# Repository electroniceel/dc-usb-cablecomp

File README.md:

12 VDC to Vusb adapter with compensation for cable resistance
=============================================================

Use a reliable 12 VDC power supply for USB-powered devices.

Dedicated USB chargers often don't have the desired reliability 
for 24/7 use over several years. Power supplies with 12 VDC output
into a DC jack are available in a reliable quality. I can recommend
Meanwell GST40A12-P1J.

USB cables often have higher resistance than
dedicated power cables, even the better ones designed for charging.
This leads to significant voltage drop at higher loads and can cause
the devices to become unstable. Also charging phones is often slower
due to the voltage drop. This adapter compensates for this by sligtly 
increasing the voltage with increasing load.

Schematics & Layout
-------------------

Schematics & Layout were done in KiCAD.

[Schematics as PDF](https://github.com/electroniceel/dc-usb-cablecomp/raw/master/schematics.pdf)

Case
----

I designed the adapter with heatshrink tube as case in mind. I used
heatshrink tube with 24mm unshrunk diameter, hotglue inside and 4:1 shrink ratio.

The label on my heatshrink tube says "PLDW 104-24/6", Reichelt order number "SDK 24,0 SW".

I cut a strip of 42mm, which fits well after shrinking.

License
-------

This work is licensed under a [Creative Commons Attribution 4.0 International License](https://creativecommons.org/licenses/by/4.0/).

Please link to https://github.com/electroniceel/dc-usb-cablecomp or https://git.io/JfeTQ for attribution.

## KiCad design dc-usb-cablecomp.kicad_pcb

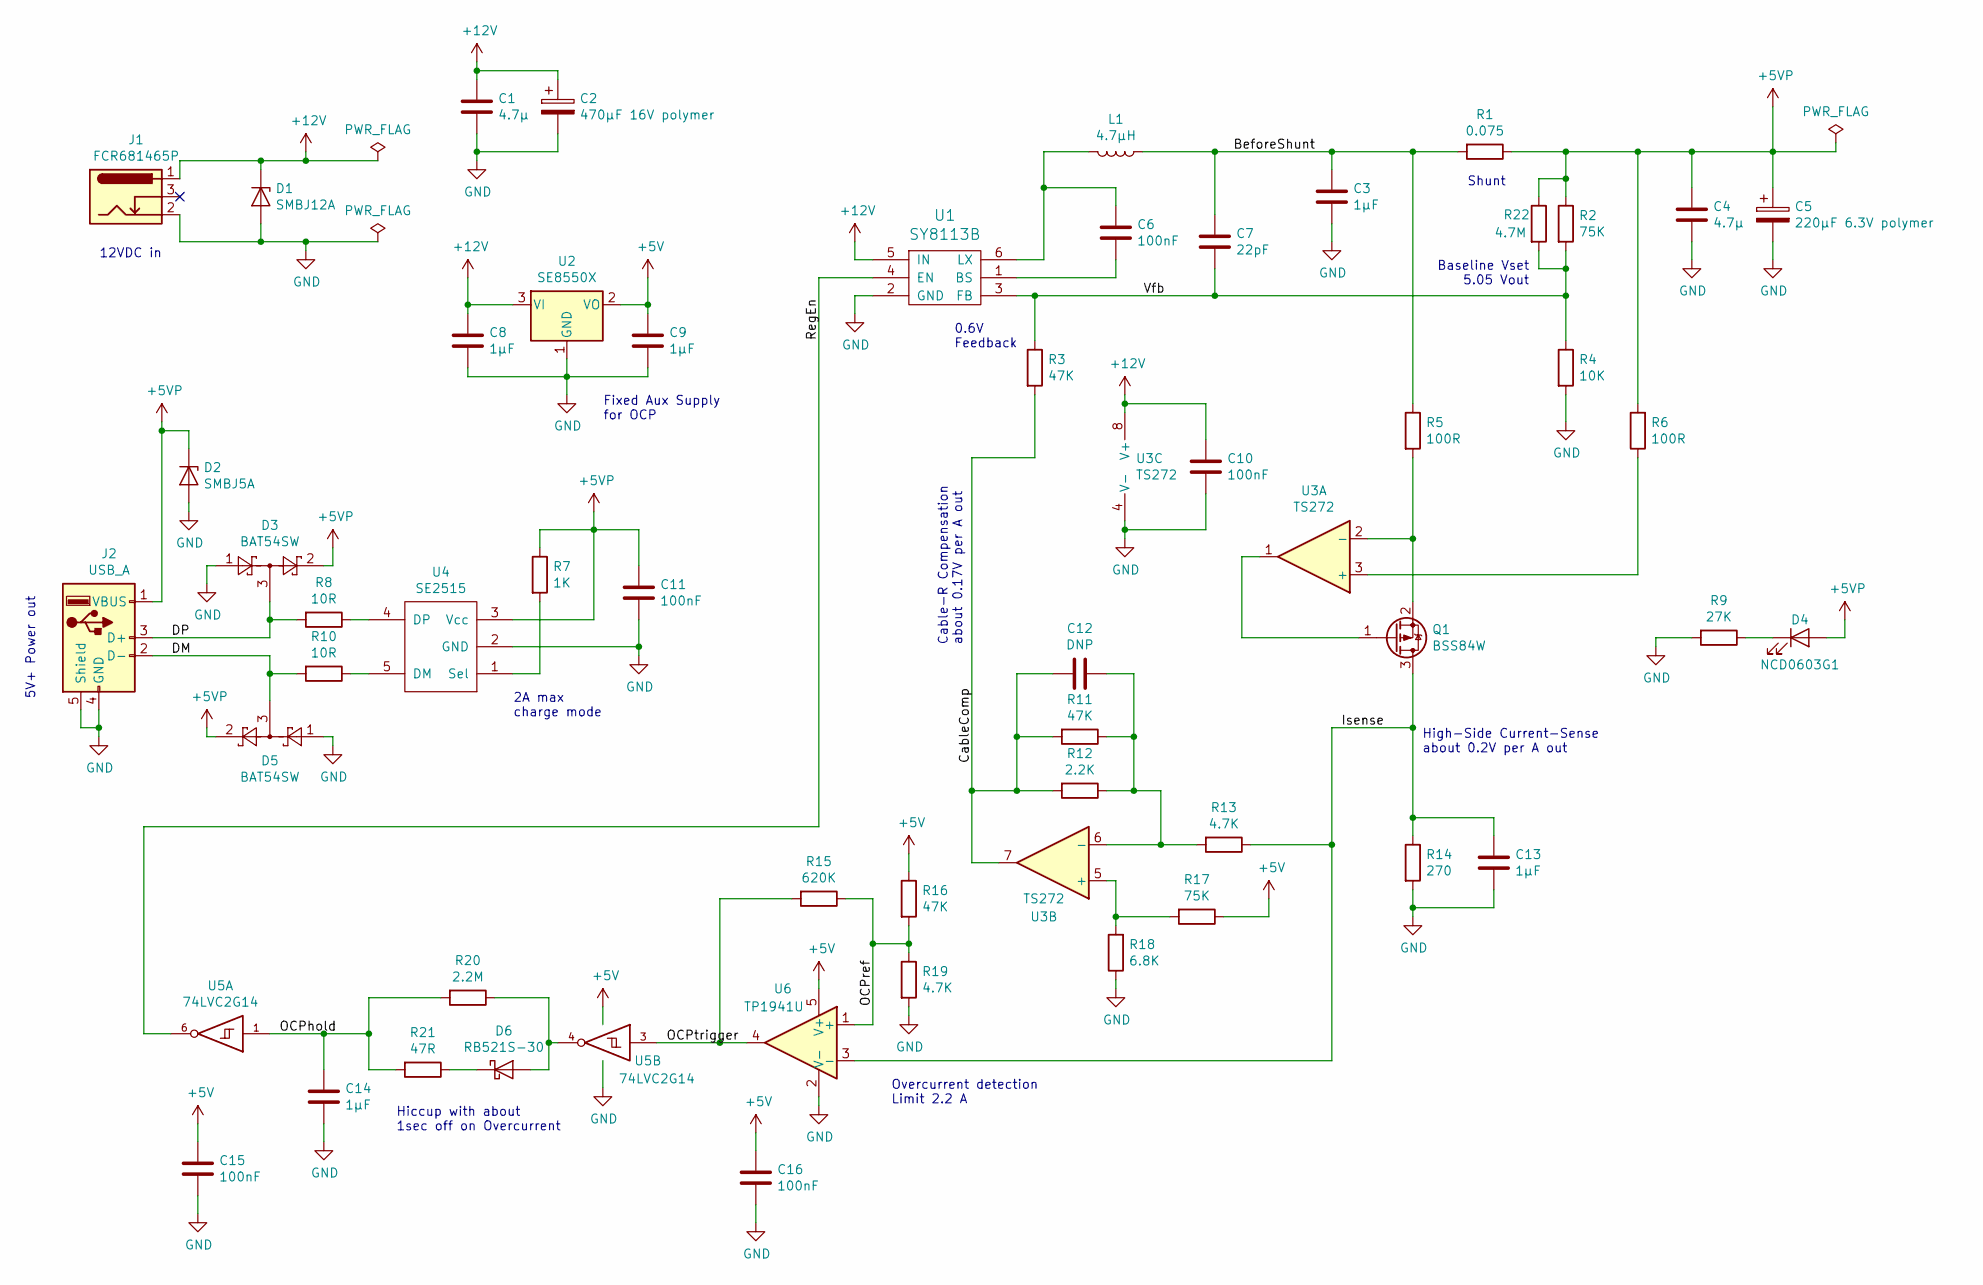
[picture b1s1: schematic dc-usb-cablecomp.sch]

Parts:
C1, C4: 4.7µ; SMD0805-wide-C
C2: 470µF 16V polymer; C_Radial_D6.3mm_H11.0mm_P2.50mm
C3, C8, C9, C13, C14: 1µF; SMD0603-wide-C
C5: 220µF 6.3V polymer; C_Radial_D5.0mm_H7.0mm_P2.00mm
C6, C10, C11, C15, C16: 100nF; SMD0603-wide-C
C7: 22pF; SMD0603-wide-C
C12: DNP; SMD0603-wide-C
D1: SMBJ12A; SMB_Diode
D2: SMBJ5A; SMB_Diode
D3, D5: BAT54SW; SOT-323-wide
D4: NCD0603G1; SMD0603-wide-diode
D6: RB521S-30; D_SOD-523
J1: FCR681465P; Cliff_FCR681465P_barrel_jack
J2: USB_A
L1: 4.7µH; Fastron-1616FPS
Q1: BSS84W; SOT-323-wide
R1: 0.075; SMD0805-wide-R
R2, R17: 75K; SMD0603-wide-R
R3, R11, R16: 47K; SMD0603-wide-R
R4: 10K; SMD0603-wide-R
R5, R6: 100R; SMD0603-wide-R
R7: 1K; SMD0603-wide-R
R8, R10: 10R; SMD0603-wide-R
R9: 27K; SMD0603-wide-R
R12: 2.2K; SMD0603-wide-R
R13, R19: 4.7K; SMD0603-wide-R
R14: 270; SMD0603-wide-R
R15: 620K; SMD0603-wide-R
R18: 6.8K; SMD0603-wide-R
R20: 2.2M; SMD0603-wide-R
R21: 47R; SMD0603-wide-R
R22: 4.7M; SMD0603-wide-R
U1: SY8113B; SOT-23-6
U2: SE8550X; SOT-23
U3: TS272; TSSOP-8_4.4x3mm_P0.65mm
U4: SE2515; SOT-23-5
U5: 74LVC2G14; SC-70-6-wide
U6: TP1941U; SC-70-5-wide

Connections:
+5V: C9.1, C15.1, C16.1, R16.1, R17.1, U2.2 (VO), U5.5 (VCC), U6.5 (V+)
+5VP: C4.1, C5.1, C11.1, D2.1 (K), D3.2, D4.2 (A), D5.2, J2.1 (VBUS), R1.1, R2.1, R6.2, R7.1, R22.1, U4.3 (Vcc)
+12V: C1.1, C2.1, C8.1, C10.1, D1.1 (K), J1.1, U1.5 (IN), U2.3 (VI), U3.8 (V+)
/BeforeShunt: C3.1, C7.1, L1.1, R1.2, R5.1
/CableComp: C12.2, R3.2, R11.2, R12.2, U3.7
/DM: D5.3, J2.2 (D-), R10.2
/DP: D3.3, J2.3 (D+), R8.2
/Isense: C13.1, Q1.3 (D), R13.1, R14.1, U6.3 (-)
/OCPhold: C14.1, R20.2, R21.2, U5.1
/OCPref: R15.1, R16.2, R19.1, U6.1 (+)
/OCPtrigger: R15.2, U5.3, U6.4
/RegEn: U1.4 (EN), U5.6
/Vfb: C7.2, R2.2, R3.1, R4.1, R22.2, U1.3 (FB)
GND: C1.2, C2.2, C3.2, C4.2, C5.2, C8.2, C9.2, C10.2, C11.2, C13.2, C14.2, C15.2, C16.2, D1.2 (A), D2.2 (A), D3.1, D5.1, J1.2, J2.4 (GND), J2.5 (Shield), R4.2, R9.2, R14.2, R18.1, R19.2, U1.2 (GND), U2.1 (GND), U3.4 (V-), U4.2 (GND), U5.2 (GND), U6.2 (V-)
unnamed: C6.1, L1.2, U1.6 (LX)
unnamed: C6.2, U1.1 (BS)
unnamed: C12.1, R11.1, R12.1, R13.2, U3.6 (-)
unnamed: D4.1 (K), R9.1
unnamed: D6.1 (K), R21.1
unnamed: D6.2 (A), R20.1, U5.4
unnamed: Q1.1 (G), U3.1
unnamed: Q1.2 (S), R5.2, U3.2 (-)
unnamed: R6.1, U3.3 (+)
unnamed: R7.2, U4.1 (Sel)
unnamed: R8.1, U4.4 (DP)
unnamed: R10.1, U4.5 (DM)
unnamed: R17.2, R18.2, U3.5 (+)

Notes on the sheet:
High-Side Current-Sense about 0.2V per A out
Shunt
Cable-R Compensation about 0.17V per A out
Baseline Vset 5.05 Vout
Overcurrent detection Limit 2.2 A
Hiccup with about 1sec off on Overcurrent
0.6V Feedback
2A max charge mode
12VDC in
5V+ Power out
Fixed Aux Supply for OCP

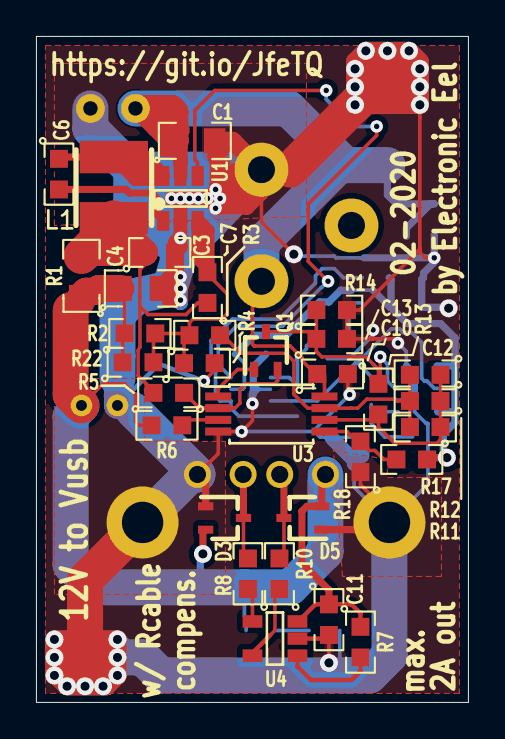
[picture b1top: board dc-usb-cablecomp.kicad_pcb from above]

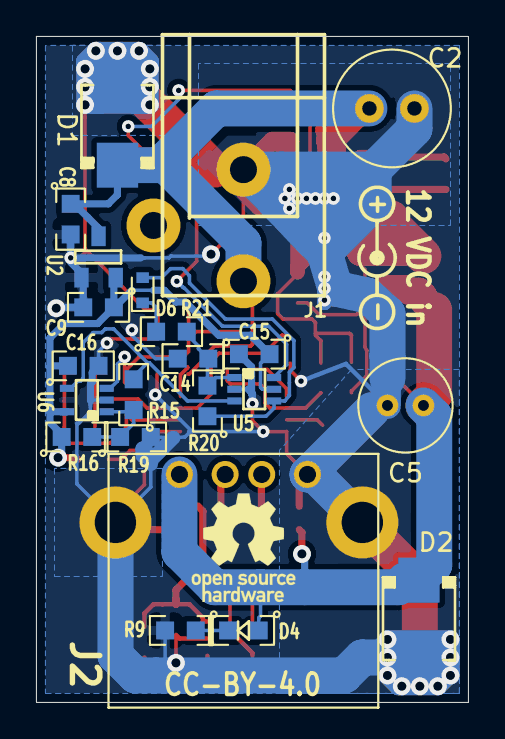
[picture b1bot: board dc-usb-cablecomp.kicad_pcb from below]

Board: 2 copper layers, 24.0 x 37.0 mm, 54 parts (22 on the bottom side), 27 nets.

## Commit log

2020-04-13 add LICENSE and initial readme
2020-04-13 Kicad project data dump
2020-04-13 add note about heatshrink case
2020-04-13 add schematics as pdf

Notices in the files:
dc-usb-cablecomp.kicad_pcb:
CC-BY-4.0
